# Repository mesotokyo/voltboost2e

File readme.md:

# Voltage Booster v2e schematic and PCB for KiCAD

(Japanese version is [here](readme_ja.md) / 日本語版は[こちら](readme_ja.md))

## What is this?

KiCAD files to build PCB of the compact voltage booster. These files are created with KiCad 6.0.

This voltage booster is intended to get DC plus/minus 9V from DC9V. The output stage also has a noise filter.

## Notice

This schematic and PCB file need a `ak_misc` footprint library in [mst-kicad-lib](https://github.com/mesotokyo/mst-kicad-lib). 

## DISCLAIMER

FILES IN THIS REPOSITORY ARE PROVIDED "AS IS", WITHOUT WARRANTY OF ANY KIND, EXPRESS OR IMPLIED, INCLUDING BUT NOT LIMITED TO THE WARRANTIES OF MERCHANTABILITY, FITNESS FOR A PARTICULAR PURPOSE AND NONINFRINGEMENT. IN NO EVENT SHALL THE AUTHORS OR COPYRIGHT HOLDERS BE LIABLE FOR ANY CLAIM, DAMAGES OR OTHER LIABILITY, WHETHER IN AN ACTION OF CONTRACT, TORT OR OTHERWISE, ARISING FROM, OUT OF OR IN CONNECTION WITH IN FILES IN THIS REPOSITORY OR THE USE OR OTHER DEALINGS IN FILES IN THIS REPOSITORY.

## License

CC BY 4.0. For more information, please check https://creativecommons.org/licenses/by/4.0/ .

## Author

MST/mesotokyo

 - https://meso.tokyo/
 - https://x.com/mesotokyox

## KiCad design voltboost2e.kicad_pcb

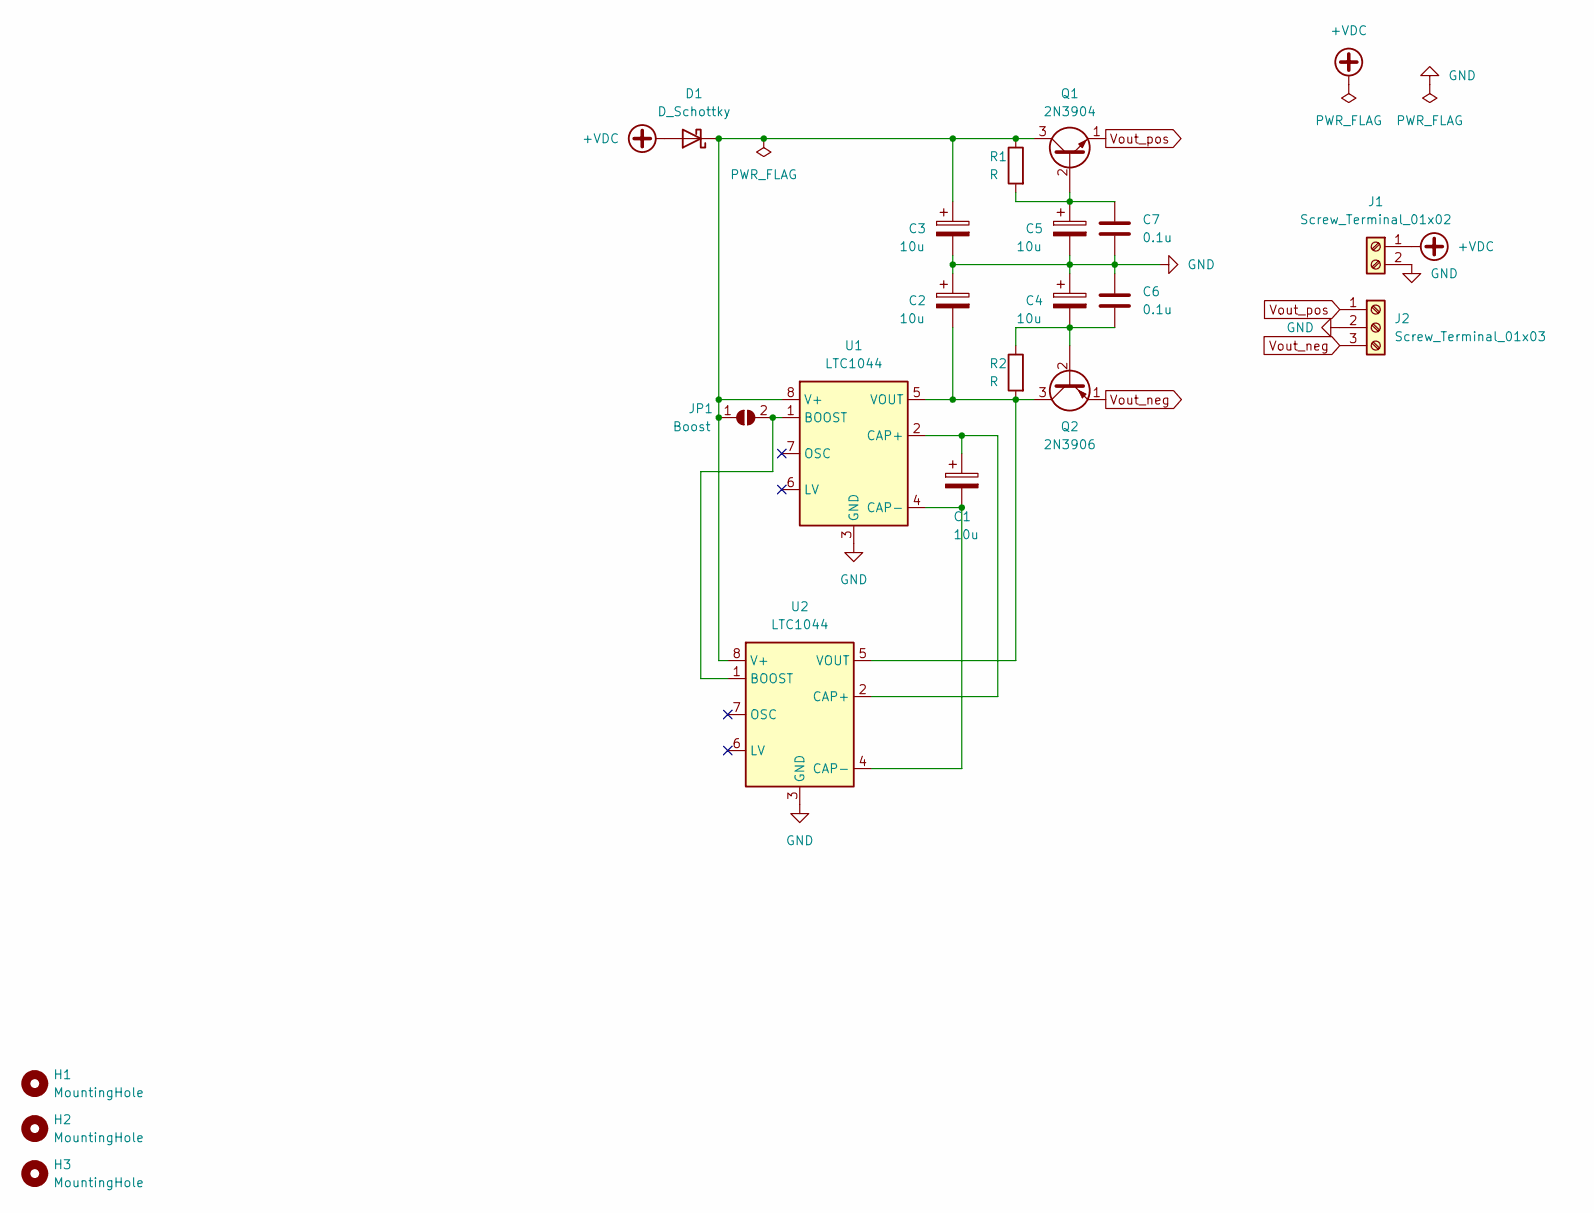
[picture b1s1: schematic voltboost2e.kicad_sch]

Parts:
C1, C2, C3, C4, C5: 10u; CP_Radial_D6.3mm_P2.50mm
C6, C7: 0.1u; C_Disc_D3.0mm_W2.0mm_P2.50mm
D1: D_Schottky; D_DO-41_SOD81_P7.62mm_Horizontal
H1, H2, H3: MountingHole; MountingHole_3.2mm_M3
J1: Screw_Terminal_01x02; TerminalBlock_Phoenix_MPT-0,5-2-2.54_1x02_P2.54mm_Horizontal
J2: Screw_Terminal_01x03; TerminalBlock_Phoenix_MPT-0,5-3-2.54_1x03_P2.54mm_Horizontal
JP1: Boost; SolderJumper-2_P1.3mm_Open_RoundedPad1.0x1.5mm
Q1: 2N3904; TO-92
Q2: 2N3906; TO-92
R1, R2: R; R_Axial_DIN0207_L6.3mm_D2.5mm_P7.62mm_with_SMD
U1: LTC1044; DIP-8_W7.62mm_Socket
U2: LTC1044; SOP-8_5.28x5.23mm_P1.27mm

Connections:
+VDC: D1.2 (A), J1.1
GND: C2.1, C3.2, C4.1, C5.2, C6.1, C7.2, J1.2, J2.2, U1.3 (GND), U2.3 (GND)
unnamed: C1.1, U1.2 (CAP+), U2.2 (CAP+)
unnamed: C1.2, U1.4 (CAP-), U2.4 (CAP-)
unnamed: C2.2, Q2.3 (C), R2.2, U1.5 (VOUT), U2.5 (VOUT)
unnamed: C3.1, D1.1 (K), JP1.1 (A), Q1.3 (C), R1.1, U1.8 (V+), U2.8 (V+)
unnamed: C4.2, C6.2, Q2.2 (B), R2.1
unnamed: C5.1, C7.1, Q1.2 (B), R1.2
unnamed: JP1.2 (B), U1.1 (BOOST), U2.1 (BOOST)
Vout_neg: J2.3, Q2.1 (E)
Vout_pos: J2.1, Q1.1 (E)

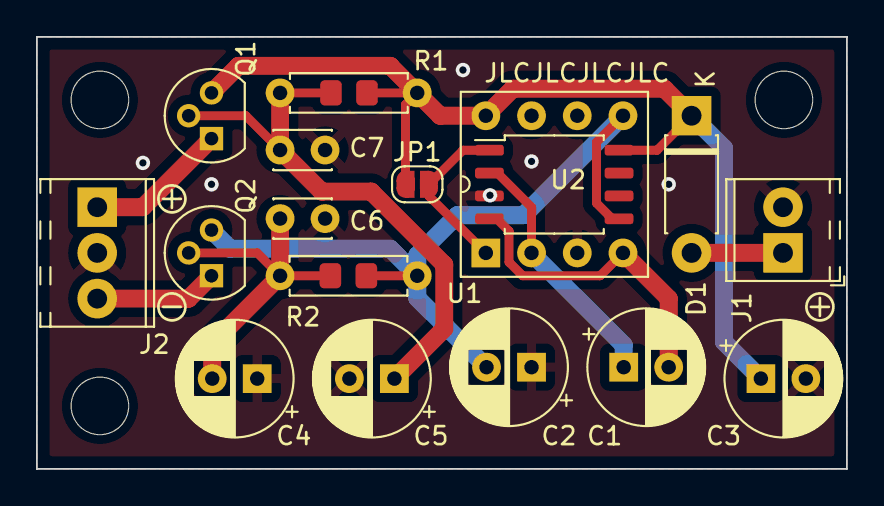
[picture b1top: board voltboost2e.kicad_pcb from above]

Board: 2 copper layers, 45.0 x 24.0 mm, 20 parts (0 on the bottom side), 11 nets.
